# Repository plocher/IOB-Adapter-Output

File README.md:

# IOB-Adapter-Generic
## License: CERN Open Hardware Licence v1.2

IOB Personality: Quad Open Drain output adapter

A 5x2 plug-in with 4x Open Drain outputs that can sink 100mA each

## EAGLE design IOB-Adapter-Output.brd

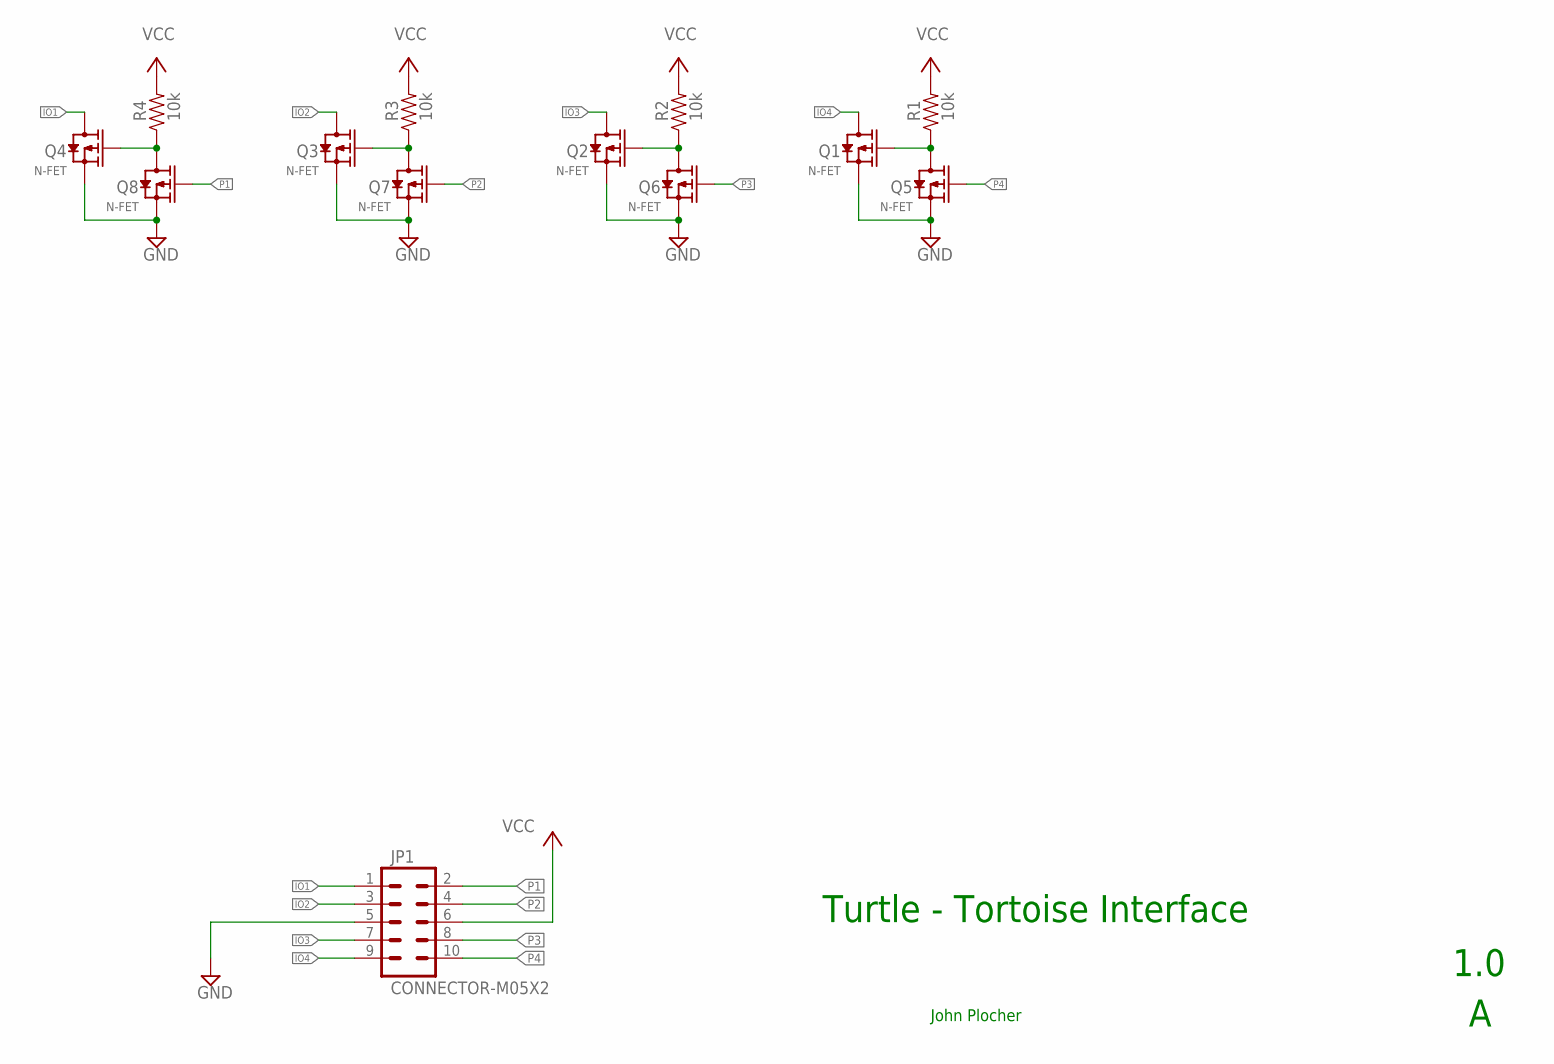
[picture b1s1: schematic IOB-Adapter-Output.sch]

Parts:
JP1: CONNECTOR-M05X2; IOB-V3-MODULE
Q1, Q2, Q3, Q4, Q5, Q6, Q7, Q8: N-FET; SOT23-3
R1, R2, R3, R4: 10k; 0805-RES

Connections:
GND: JP1.5, Q1.2 (S), Q2.2 (S), Q3.2 (S), Q4.2 (S), Q5.2 (S), Q6.2 (S), Q7.2 (S), Q8.2 (S)
IO1: JP1.1, Q4.3 (D)
IO2: JP1.3, Q3.3 (D)
IO3: JP1.7, Q2.3 (D)
IO4: JP1.9, Q1.3 (D)
unnamed: Q4.1 (G), Q8.3 (D), R4.1
unnamed: Q3.1 (G), Q7.3 (D), R3.1
unnamed: Q2.1 (G), Q6.3 (D), R2.1
unnamed: Q1.1 (G), Q5.3 (D), R1.1
P1: JP1.2, Q8.1 (G)
P2: JP1.4, Q7.1 (G)
P3: JP1.8, Q6.1 (G)
P4: JP1.10, Q5.1 (G)
VCC: JP1.6, R1.2, R2.2, R3.2, R4.2

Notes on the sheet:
Turtle - Tortoise Interface
1.0
John Plocher

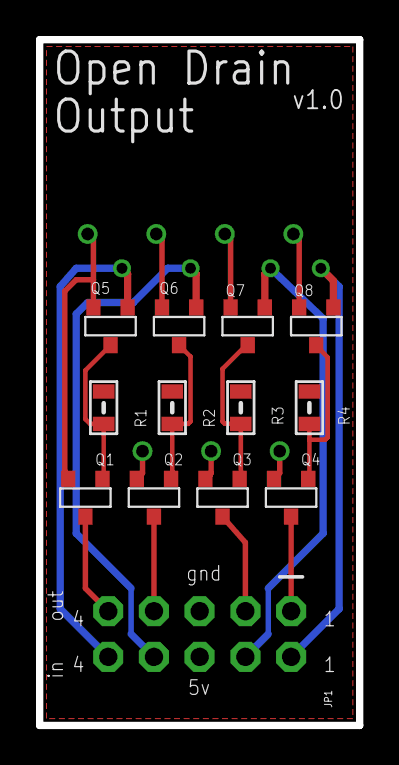
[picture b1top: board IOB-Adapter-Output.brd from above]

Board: 2 copper layers, 17.8 x 38.1 mm, 13 parts (1 on the bottom side), 14 nets.

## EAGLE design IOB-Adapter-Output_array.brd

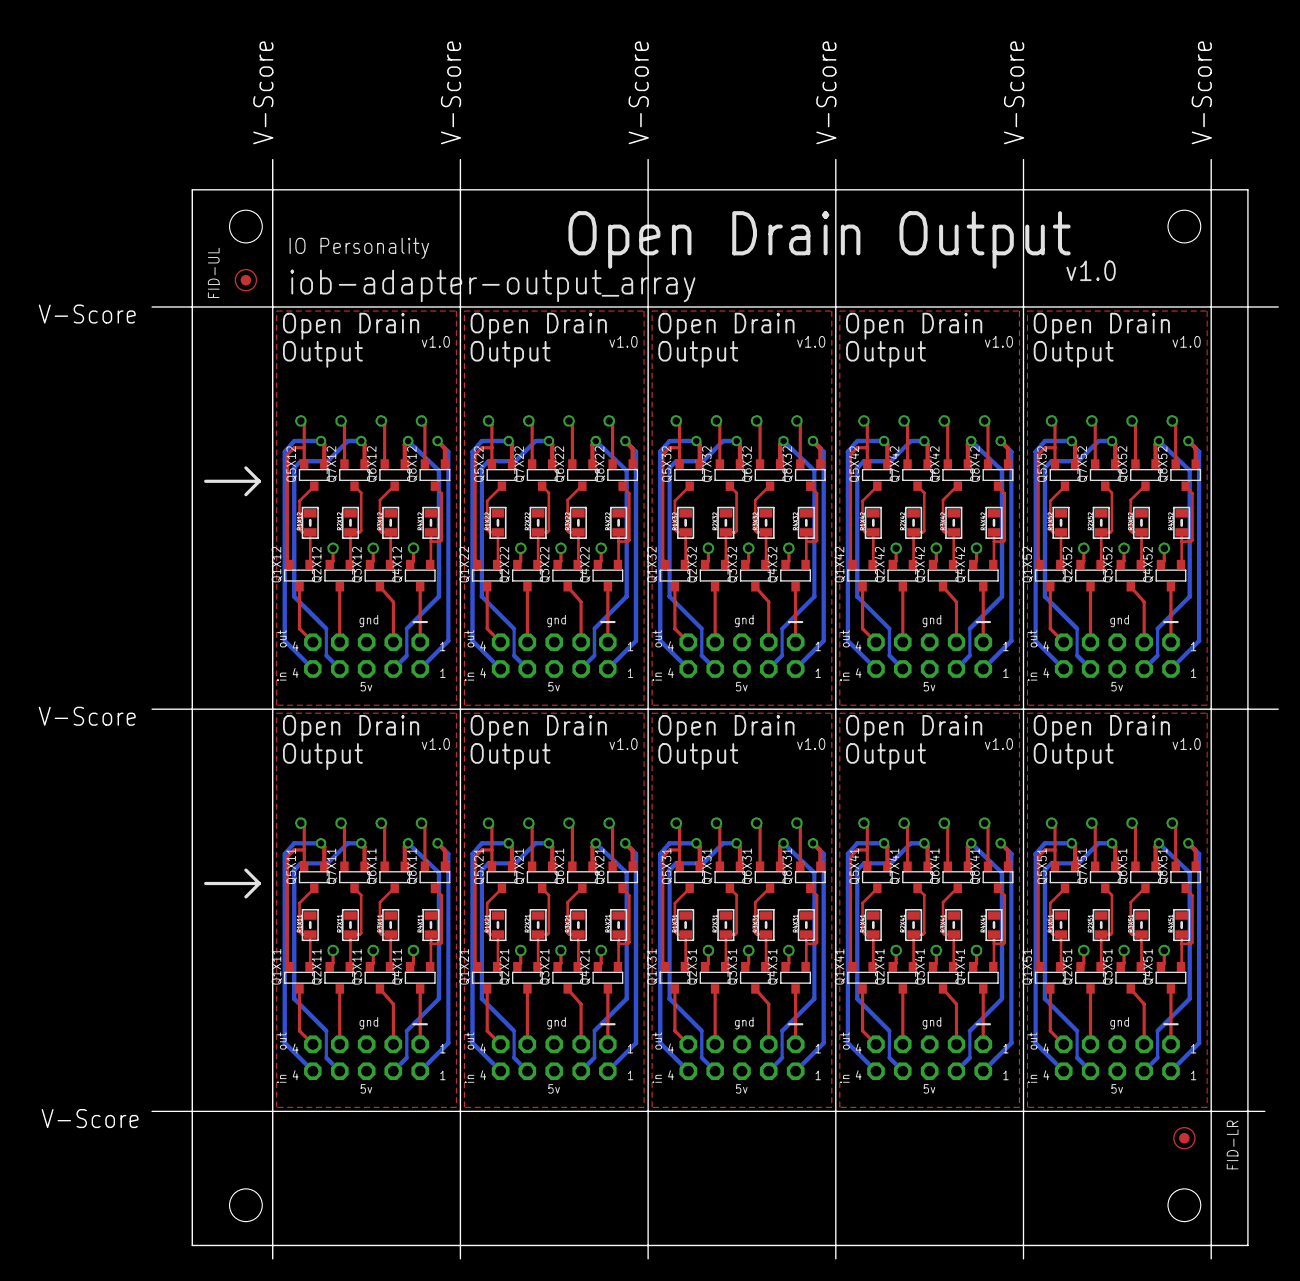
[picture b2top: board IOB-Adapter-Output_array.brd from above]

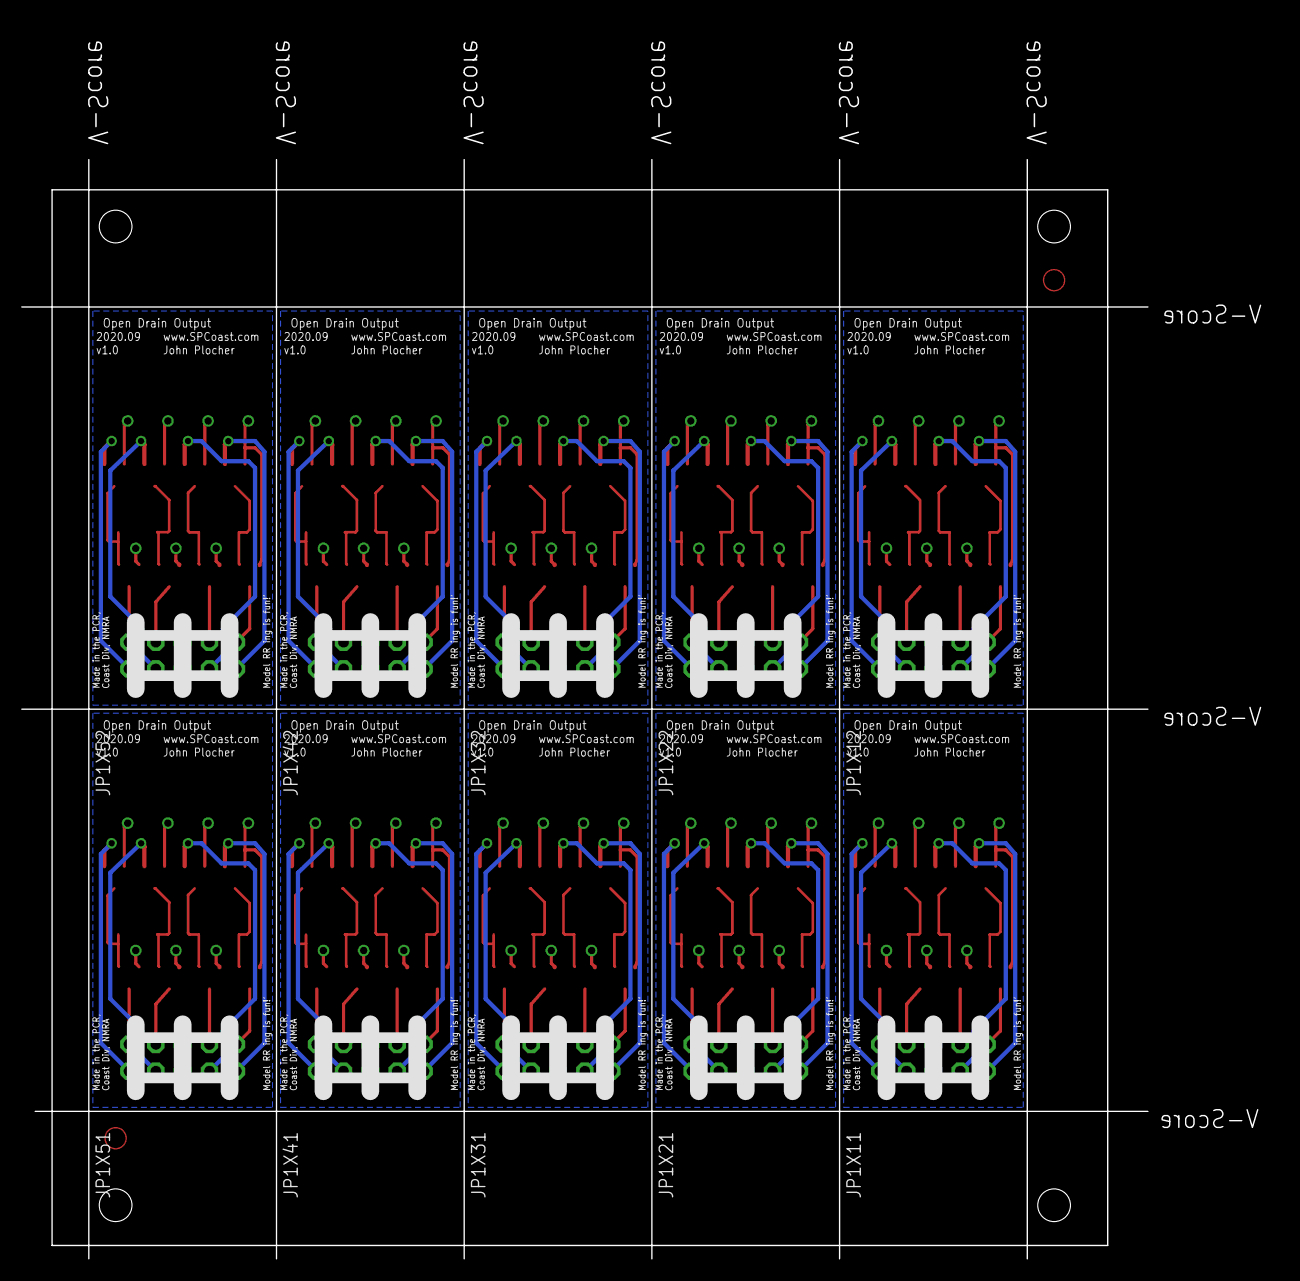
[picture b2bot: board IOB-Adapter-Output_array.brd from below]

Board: 2 copper layers, 119.0 x 117.2 mm, 133 parts (10 on the bottom side), 140 nets.

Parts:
CARRIER: BOARD; BOARD-DINRAIL-3.17IN-5X2-IOP
FID-LR: FIDUCIAL; FIDUCIAL_1MM
FID-UL: FIDUCIAL; FIDUCIAL_1MM
JP1X11, JP1X12, JP1X21, JP1X22, JP1X31, JP1X32, JP1X41, JP1X42, JP1X51, JP1X52: CONNECTOR-M05X2; IOB-V3-MODULE
Q1X11, Q1X12, Q1X21, Q1X22, Q1X31, Q1X32, Q1X41, Q1X42, Q1X51, Q1X52, Q2X11, Q2X12, Q2X21, Q2X22, Q2X31, Q2X32, Q2X41, Q2X42, Q2X51, Q2X52, Q3X11, Q3X12, Q3X21, Q3X22, Q3X31, Q3X32, Q3X41, Q3X42, Q3X51, Q3X52, Q4X11, Q4X12, Q4X21, Q4X22, Q4X31, Q4X32, Q4X41, Q4X42, Q4X51, Q4X52, Q5X11, Q5X12, Q5X21, Q5X22, Q5X31, Q5X32, Q5X41, Q5X42, Q5X51, Q5X52, Q6X11, Q6X12, Q6X21, Q6X22, Q6X31, Q6X32, Q6X41, Q6X42, Q6X51, Q6X52, Q7X11, Q7X12, Q7X21, Q7X22, Q7X31, Q7X32, Q7X41, Q7X42, Q7X51, Q7X52, Q8X11, Q8X12, Q8X21, Q8X22, Q8X31, Q8X32, Q8X41, Q8X42, Q8X51, Q8X52: N-FET; SOT23-3
R1X11, R1X12, R1X21, R1X22, R1X31, R1X32, R1X41, R1X42, R1X51, R1X52, R2X11, R2X12, R2X21, R2X22, R2X31, R2X32, R2X41, R2X42, R2X51, R2X52, R3X11, R3X12, R3X21, R3X22, R3X31, R3X32, R3X41, R3X42, R3X51, R3X52, R4X11, R4X12, R4X21, R4X22, R4X31, R4X32, R4X41, R4X42, R4X51, R4X52: 10k; 0805-RES

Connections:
GNDX11: JP1X11.5, Q1X11.2, Q2X11.2, Q3X11.2, Q4X11.2, Q5X11.2, Q6X11.2, Q7X11.2, Q8X11.2
GNDX12: JP1X12.5, Q1X12.2, Q2X12.2, Q3X12.2, Q4X12.2, Q5X12.2, Q6X12.2, Q7X12.2, Q8X12.2
GNDX21: JP1X21.5, Q1X21.2, Q2X21.2, Q3X21.2, Q4X21.2, Q5X21.2, Q6X21.2, Q7X21.2, Q8X21.2
GNDX22: JP1X22.5, Q1X22.2, Q2X22.2, Q3X22.2, Q4X22.2, Q5X22.2, Q6X22.2, Q7X22.2, Q8X22.2
GNDX31: JP1X31.5, Q1X31.2, Q2X31.2, Q3X31.2, Q4X31.2, Q5X31.2, Q6X31.2, Q7X31.2, Q8X31.2
GNDX32: JP1X32.5, Q1X32.2, Q2X32.2, Q3X32.2, Q4X32.2, Q5X32.2, Q6X32.2, Q7X32.2, Q8X32.2
GNDX41: JP1X41.5, Q1X41.2, Q2X41.2, Q3X41.2, Q4X41.2, Q5X41.2, Q6X41.2, Q7X41.2, Q8X41.2
GNDX42: JP1X42.5, Q1X42.2, Q2X42.2, Q3X42.2, Q4X42.2, Q5X42.2, Q6X42.2, Q7X42.2, Q8X42.2
GNDX51: JP1X51.5, Q1X51.2, Q2X51.2, Q3X51.2, Q4X51.2, Q5X51.2, Q6X51.2, Q7X51.2, Q8X51.2
GNDX52: JP1X52.5, Q1X52.2, Q2X52.2, Q3X52.2, Q4X52.2, Q5X52.2, Q6X52.2, Q7X52.2, Q8X52.2
IO1X11: JP1X11.1, Q4X11.3
IO1X12: JP1X12.1, Q4X12.3
IO1X21: JP1X21.1, Q4X21.3
IO1X22: JP1X22.1, Q4X22.3
IO1X31: JP1X31.1, Q4X31.3
IO1X32: JP1X32.1, Q4X32.3
IO1X41: JP1X41.1, Q4X41.3
IO1X42: JP1X42.1, Q4X42.3
IO1X51: JP1X51.1, Q4X51.3
IO1X52: JP1X52.1, Q4X52.3
IO2X11: JP1X11.3, Q3X11.3
IO2X12: JP1X12.3, Q3X12.3
IO2X21: JP1X21.3, Q3X21.3
IO2X22: JP1X22.3, Q3X22.3
IO2X31: JP1X31.3, Q3X31.3
IO2X32: JP1X32.3, Q3X32.3
IO2X41: JP1X41.3, Q3X41.3
IO2X42: JP1X42.3, Q3X42.3
IO2X51: JP1X51.3, Q3X51.3
IO2X52: JP1X52.3, Q3X52.3
IO3X11: JP1X11.7, Q2X11.3
IO3X12: JP1X12.7, Q2X12.3
IO3X21: JP1X21.7, Q2X21.3
IO3X22: JP1X22.7, Q2X22.3
IO3X31: JP1X31.7, Q2X31.3
IO3X32: JP1X32.7, Q2X32.3
IO3X41: JP1X41.7, Q2X41.3
IO3X42: JP1X42.7, Q2X42.3
IO3X51: JP1X51.7, Q2X51.3
IO3X52: JP1X52.7, Q2X52.3
IO4X11: JP1X11.9, Q1X11.3
IO4X12: JP1X12.9, Q1X12.3
IO4X21: JP1X21.9, Q1X21.3
IO4X22: JP1X22.9, Q1X22.3
IO4X31: JP1X31.9, Q1X31.3
IO4X32: JP1X32.9, Q1X32.3
IO4X41: JP1X41.9, Q1X41.3
IO4X42: JP1X42.9, Q1X42.3
IO4X51: JP1X51.9, Q1X51.3
IO4X52: JP1X52.9, Q1X52.3
unnamed: Q4X11.1, Q8X11.3, R4X11.1
unnamed: Q4X12.1, Q8X12.3, R4X12.1
unnamed: Q4X21.1, Q8X21.3, R4X21.1
unnamed: Q4X22.1, Q8X22.3, R4X22.1
unnamed: Q4X31.1, Q8X31.3, R4X31.1
unnamed: Q4X32.1, Q8X32.3, R4X32.1
unnamed: Q4X41.1, Q8X41.3, R4X41.1
unnamed: Q4X42.1, Q8X42.3, R4X42.1
unnamed: Q4X51.1, Q8X51.3, R4X51.1
unnamed: Q4X52.1, Q8X52.3, R4X52.1
unnamed: Q3X11.1, Q6X11.3, R3X11.1
unnamed: Q3X12.1, Q6X12.3, R3X12.1
unnamed: Q3X21.1, Q6X21.3, R3X21.1
unnamed: Q3X22.1, Q6X22.3, R3X22.1
unnamed: Q3X31.1, Q6X31.3, R3X31.1
unnamed: Q3X32.1, Q6X32.3, R3X32.1
unnamed: Q3X41.1, Q6X41.3, R3X41.1
unnamed: Q3X42.1, Q6X42.3, R3X42.1
unnamed: Q3X51.1, Q6X51.3, R3X51.1
unnamed: Q3X52.1, Q6X52.3, R3X52.1
unnamed: Q2X11.1, Q7X11.3, R2X11.1
unnamed: Q2X12.1, Q7X12.3, R2X12.1
unnamed: Q2X21.1, Q7X21.3, R2X21.1
unnamed: Q2X22.1, Q7X22.3, R2X22.1
unnamed: Q2X31.1, Q7X31.3, R2X31.1
unnamed: Q2X32.1, Q7X32.3, R2X32.1
unnamed: Q2X41.1, Q7X41.3, R2X41.1
unnamed: Q2X42.1, Q7X42.3, R2X42.1
unnamed: Q2X51.1, Q7X51.3, R2X51.1
unnamed: Q2X52.1, Q7X52.3, R2X52.1
unnamed: Q1X11.1, Q5X11.3, R1X11.1
unnamed: Q1X12.1, Q5X12.3, R1X12.1
unnamed: Q1X21.1, Q5X21.3, R1X21.1
unnamed: Q1X22.1, Q5X22.3, R1X22.1
unnamed: Q1X31.1, Q5X31.3, R1X31.1
unnamed: Q1X32.1, Q5X32.3, R1X32.1
unnamed: Q1X41.1, Q5X41.3, R1X41.1
unnamed: Q1X42.1, Q5X42.3, R1X42.1
unnamed: Q1X51.1, Q5X51.3, R1X51.1
unnamed: Q1X52.1, Q5X52.3, R1X52.1
P1X11: JP1X11.2, Q8X11.1
P1X12: JP1X12.2, Q8X12.1
P1X21: JP1X21.2, Q8X21.1
P1X22: JP1X22.2, Q8X22.1
P1X31: JP1X31.2, Q8X31.1
P1X32: JP1X32.2, Q8X32.1
P1X41: JP1X41.2, Q8X41.1
P1X42: JP1X42.2, Q8X42.1
P1X51: JP1X51.2, Q8X51.1
P1X52: JP1X52.2, Q8X52.1
P2X11: JP1X11.4, Q6X11.1
P2X12: JP1X12.4, Q6X12.1
P2X21: JP1X21.4, Q6X21.1
P2X22: JP1X22.4, Q6X22.1
P2X31: JP1X31.4, Q6X31.1
P2X32: JP1X32.4, Q6X32.1
P2X41: JP1X41.4, Q6X41.1
P2X42: JP1X42.4, Q6X42.1
P2X51: JP1X51.4, Q6X51.1
P2X52: JP1X52.4, Q6X52.1
P3X11: JP1X11.8, Q7X11.1
P3X12: JP1X12.8, Q7X12.1
P3X21: JP1X21.8, Q7X21.1
P3X22: JP1X22.8, Q7X22.1
P3X31: JP1X31.8, Q7X31.1
P3X32: JP1X32.8, Q7X32.1
P3X41: JP1X41.8, Q7X41.1
P3X42: JP1X42.8, Q7X42.1
P3X51: JP1X51.8, Q7X51.1
P3X52: JP1X52.8, Q7X52.1
P4X11: JP1X11.10, Q5X11.1
P4X12: JP1X12.10, Q5X12.1
P4X21: JP1X21.10, Q5X21.1
P4X22: JP1X22.10, Q5X22.1
P4X31: JP1X31.10, Q5X31.1
P4X32: JP1X32.10, Q5X32.1
P4X41: JP1X41.10, Q5X41.1
P4X42: JP1X42.10, Q5X42.1
P4X51: JP1X51.10, Q5X51.1
P4X52: JP1X52.10, Q5X52.1
VCCX11: JP1X11.6, R1X11.2, R2X11.2, R3X11.2, R4X11.2
VCCX12: JP1X12.6, R1X12.2, R2X12.2, R3X12.2, R4X12.2
VCCX21: JP1X21.6, R1X21.2, R2X21.2, R3X21.2, R4X21.2
VCCX22: JP1X22.6, R1X22.2, R2X22.2, R3X22.2, R4X22.2
VCCX31: JP1X31.6, R1X31.2, R2X31.2, R3X31.2, R4X31.2
VCCX32: JP1X32.6, R1X32.2, R2X32.2, R3X32.2, R4X32.2
VCCX41: JP1X41.6, R1X41.2, R2X41.2, R3X41.2, R4X41.2
VCCX42: JP1X42.6, R1X42.2, R2X42.2, R3X42.2, R4X42.2
VCCX51: JP1X51.6, R1X51.2, R2X51.2, R3X51.2, R4X51.2
VCCX52: JP1X52.6, R1X52.2, R2X52.2, R3X52.2, R4X52.2

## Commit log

2020-09-18 Initial version
2020-09-18 typo in silkscreen
2020-09-18 added Graphic
2020-10-05 added values for connectors
2020-10-06 normalized values
